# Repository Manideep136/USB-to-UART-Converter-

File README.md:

# USB-to-UART-Converter

A compact USB-to-UART converter PCB designed for communication between a computer and microcontroller-based systems such as STM32, ESP32, Arduino, and other embedded development boards.

Features
USB interface for connection to a PC or laptop
UART serial communication interface
TX and RX signal breakout
Compact PCB design
Designed using KiCad
Suitable for programming, debugging, and serial communication
Easy connection to 3.3 V / 5 V UART-based systems
Applications

This USB-to-UART converter can be used for:

STM32 development and debugging
ESP32 serial communication
Arduino development
Embedded-system debugging
Serial terminal communication
Firmware programming
UART-based sensor/module communication
Interface
USB Side

The USB interface provides:

USB 5 V power
USB D+
USB D−
GND

PCB Design

The PCB was designed using KiCad, including:

Schematic design
Component selection
PCB layout
Routing
Design Rule Check (DRC)
Gerber generation

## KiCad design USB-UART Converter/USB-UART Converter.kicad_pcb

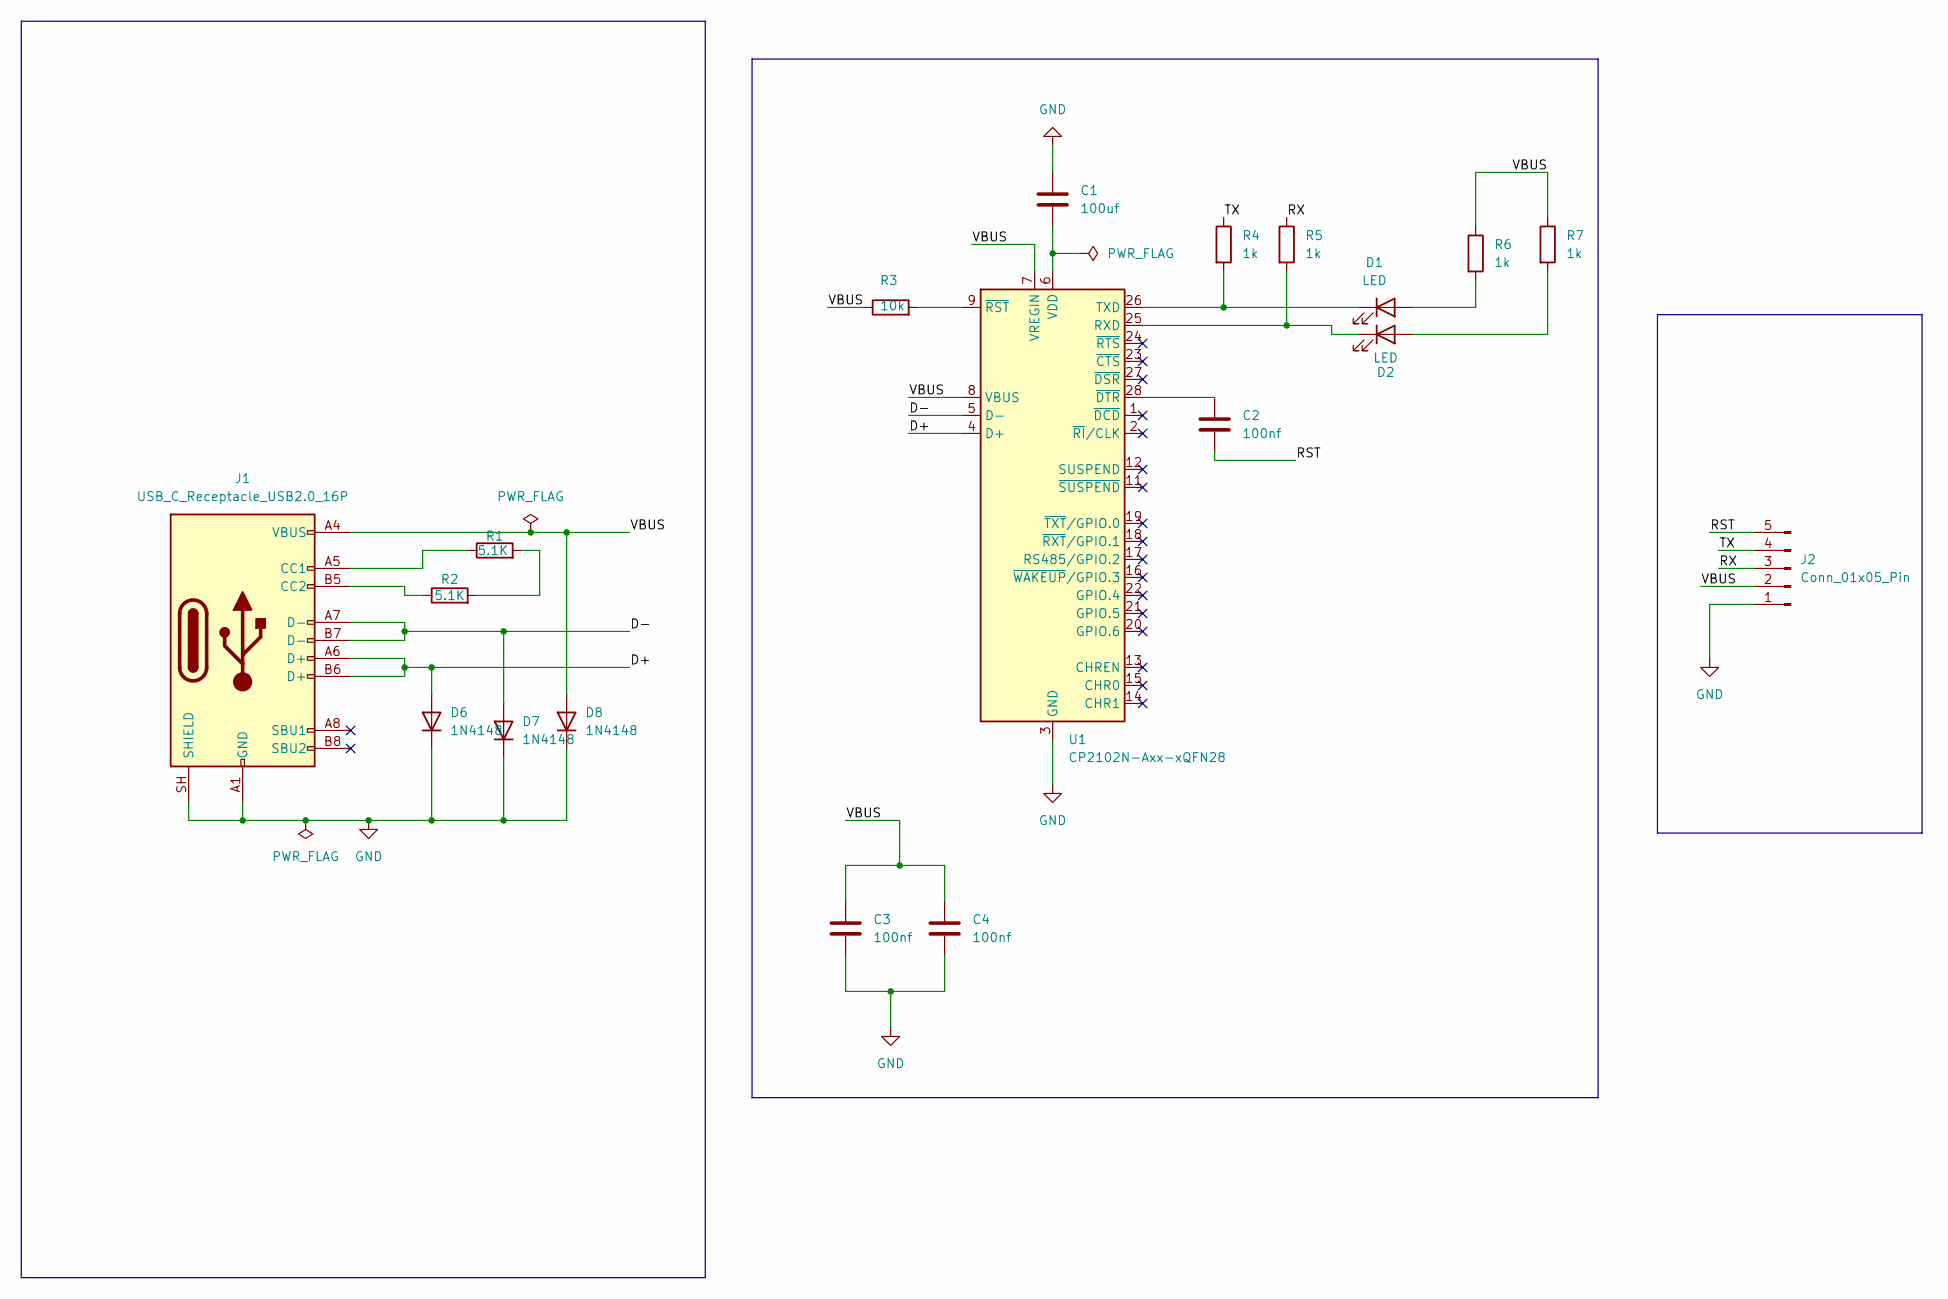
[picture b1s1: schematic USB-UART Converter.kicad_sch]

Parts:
C1: 100uf; C_0603_1608Metric
C2, C3, C4: 100nf; C_0603_1608Metric
D1, D2: LED; LED_0201_0603Metric
D6, D7, D8: 1N4148; D_DO-35_SOD27_P7.62mm_Horizontal
J1: USB_C_Receptacle_USB2.0_16P; USB_C_Receptacle_HRO_TYPE-C-31-M-12
J2: Conn_01x05_Pin; PinHeader_1x05_P2.54mm_Horizontal
R1, R2: 5.1K; R_0201_0603Metric
R3: 10k; R_0201_0603Metric
R4, R5, R6, R7: 1k; R_0201_0603Metric
U1: CP2102N-Axx-xQFN28; QFN-28-1EP_5x5mm_P0.5mm_EP3.35x3.35mm

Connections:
/<NO NET>: D7.2 (A), J1.A7 (D-), J1.B7 (D-), U1.5 (D-)
/D+: D6.2 (A), J1.A6 (D+), J1.B6 (D+), U1.4 (D+)
/RST: C2.2, J2.5
/RX: J2.3, R5.1
/TX: J2.4, R4.1
/VBUS: C3.1, C4.1, D8.2 (A), J1.A4 (VBUS), J1.A9 (VBUS), J1.B4 (VBUS), J1.B9 (VBUS), J2.2, R3.1, R6.1, R7.1, U1.7 (VREGIN), U1.8 (VBUS)
GND: C1.1, C3.2, C4.2, D6.1 (K), D7.1 (K), D8.1 (K), J1.A1 (GND), J1.A12 (GND), J1.B1 (GND), J1.B12 (GND), J1.SH (SHIELD), J2.1, U1.3 (GND), U1.29 (GND)
unnamed: D1.2 (A), R6.2
unnamed: D1.1 (K), R4.2, U1.26 (TXD)
unnamed: D2.2 (A), R7.2
unnamed: D2.1 (K), R5.2, U1.25 (RXD)
unnamed: J1.A5 (CC1), R1.1
unnamed: J1.B5 (CC2), R2.1
unnamed: R1.2, R2.2
unnamed: C1.2, U1.6 (VDD)
unnamed: C2.1, U1.28 (~DTR)
unnamed: R3.2, U1.9 (~RST)

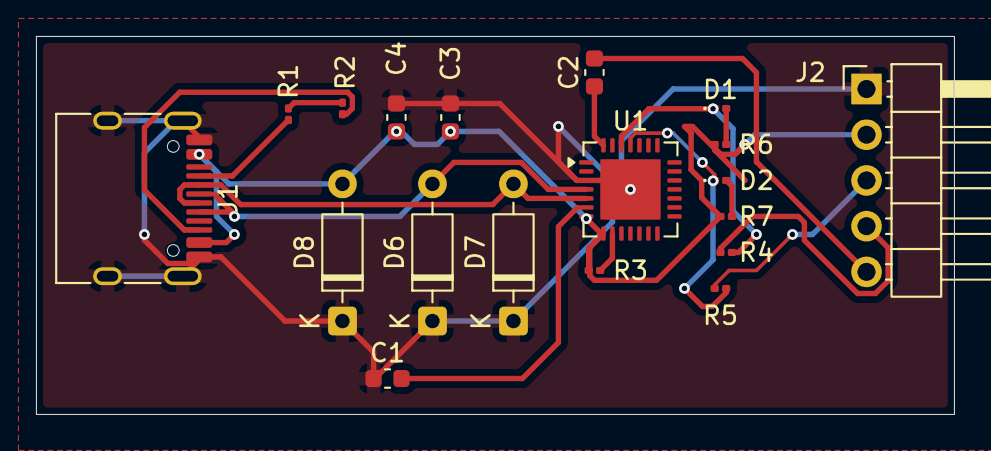
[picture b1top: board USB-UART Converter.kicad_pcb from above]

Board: 2 copper layers, 51.0 x 21.0 mm, 19 parts (0 on the bottom side), 17 nets.
